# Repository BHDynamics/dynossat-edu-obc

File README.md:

# DynOSSAT-EDU-OBC (On-Board Computer)

**Important note: we have updated the Arduino Boards Manager link.** Please update your Arduino IDE settings with our new link: https://bhdynamics.github.io/board_index/package_bhdynamics_index.json since the previous one (https://bhdynamics.github.io/board_index/package_dynossat_index.json) **NO LONGER WORKS**.

DynOSSAT-EDU is the first open source PocketQube educational kit compatible with CircuitPython and Arduino.

This plaform is equipped with all the necessary modules for the operation of a nanosatellite (PocketQube)
in Low Earth Orbit (LEO) that would serve as a device for teaching, training, and driving curiosity about the philosophy and technology related to NewSpace.

This repository contains the hardware files for the OBC (On-Board Computer), the module responsible for managing the satellite and process sensor data. It
integrates a 9-axis IMU and carries a powerful ATSAMD51.

Hardware in this repository is licenced under **CERN OHL v1.2**.

## Technical details

- Powerful ATSAMD51J20A-AU 120 MHz Cortex-M4F processor with 1 MB flash + 256 KB RAM for all your CircuitPython needs
- 32 Mbit SPI flash for storing CircuitPython code and libraries
- High-precision ICM-20948 Inertial Measurement Unit including Accelerometer, Gyroscope and Magnetometer for Attitude management
- MCP9808 Digital Temperature Sensor
- SGP30 TVOC and eqCO2 air quality sensor
- User-controllable WS2812B addressable RGB LED
- Separate 5V and 3.3V rails, providing up to 1A/500mA respectively
- MicroSD Card slot
- Female USB-C 2.0 connector for power and data logging
- PQBH40 bus exposing 10 digital pins, 6 analog pins (+ true DAC), an I2C bus, an SPI bus and an UART

## Documentation

Available in this repo's [Wiki](https://github.com/BHDynamics/dynossat-edu-obc/wiki).

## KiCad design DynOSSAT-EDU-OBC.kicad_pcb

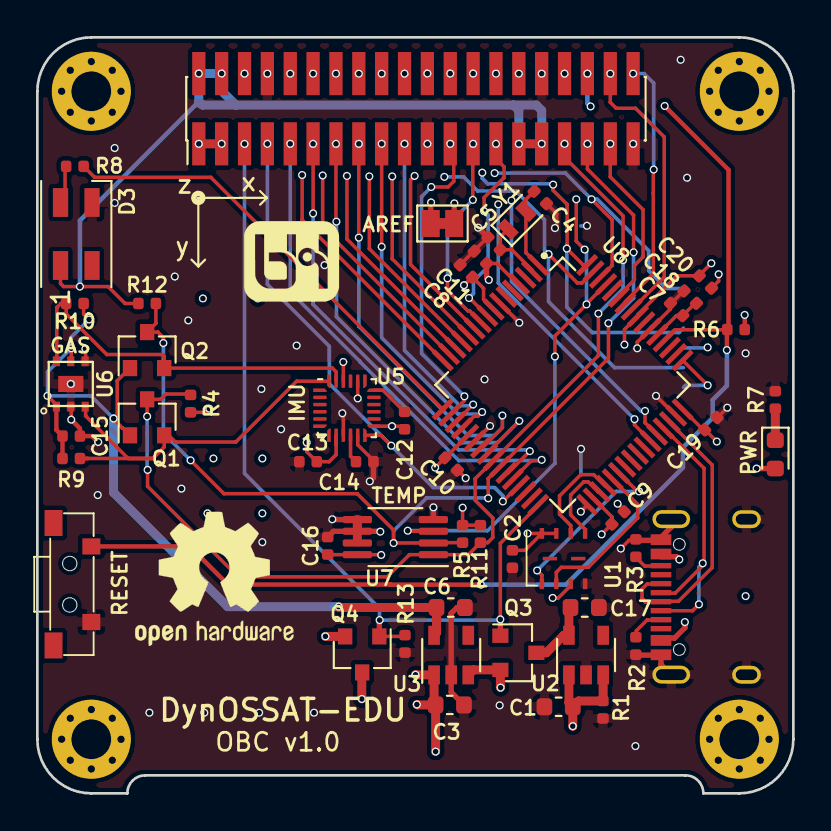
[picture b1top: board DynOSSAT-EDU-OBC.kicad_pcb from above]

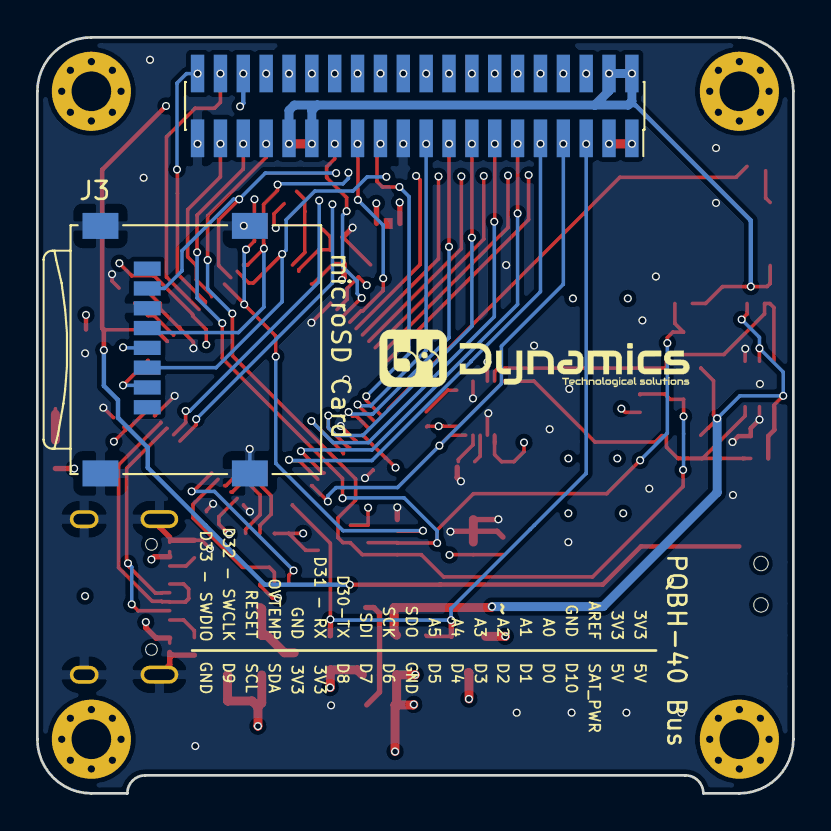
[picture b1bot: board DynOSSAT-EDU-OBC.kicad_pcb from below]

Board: 4 copper layers, 42.0 x 42.0 mm, 57 parts (2 on the bottom side), 54 nets.

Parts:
C1, C3, C6, C17: 10uF; C_0603_1608Metric
C2, C8, C11, C12, C13, C14, C15, C16, C18, C19, C20: 100nF; C_0402_1005Metric
C4, C5: 22pF; C_0402_1005Metric
C7, C9: 4.7uF; C_0402_1005Metric
C10: 1uF; C_0402_1005Metric
D2: Red; LED_0603_1608Metric
D3: WS2812B; LED_SK6812MINI_PLCC4_3.5x3.5mm_P1.75mm
H1, H2, H3, H4: MountingHole_Pad; MountingHole_2.2mm_M2_Pad_Via
J1: Main Bus; PinHeader_2x20_P1.27mm_Vertical_SMD
J2: Main Bus; PinSocket_2x20_P1.27mm_Vertical_SMD
J3: Micro_SD_Card; TF-102-18
J4: USB_C_Receptacle_USB2.0; U262-161N-4BVC11
JP2: Jumper; SolderJumper-2_P1.3mm_Bridged_Pad1.0x1.5mm
Q1, Q2: BSS138; SOT-23
Q3, Q4: DMG2305L; SOT-23
R1, R6, R13: 100k; R_0402_1005Metric
R2, R3: 5.1k; R_0402_1005Metric
R4, R5, R9, R10, R11, R12: 10k; R_0402_1005Metric
R7: 510; R_0402_1005Metric
R8: 510R; R_0402_1005Metric
SW1: RESET; 1TS002G-1800-3500-CT
U1: GD25Q32; WSON-8-1EP_3x4mm_P0.8mm
U2: ME6211C33; SOT-23-5
U3: ME6211C; SOT-23-5
U5: ICM-20948; QFN-24-1EP_3x3mm_P0.4mm_EP1.75x1.6mm
U6: SGP30
U7: MCP9808; MSOP-8_3x3mm_P0.65mm
U8: ATSAMD51J20A-AU; QFP50P1200X1200X120-64N
Y1: 32.768k - 12.5pF; Crystal_SMD_2012-2Pin_2.0x1.2mm

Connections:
+1V8: C6.1, C12.1, C13.1, C15.1, Q1.1, Q2.1, R9.1, R10.1, U3.5, U5.8, U5.13, U5.22, U6.1, U6.5
+3V3_SAT: C2.1, C3.1, C8.1, C9.1, C10.1, C16.1, C19.1, C20.1, D2.2, D3.1, J1.2, J1.4, J1.29, J1.31, J2.2, J2.4, J2.29, J2.31, J3.4, JP2.1, Q3.2, R4.2, R5.2, R6.2, R11.1, R12.1, U1.3, U1.7, U1.8, U3.1, U3.3, U7.8, U8.8, U8.21, U8.34, U8.48, U8.56
+5V_SAT: C1.1, J1.1, J1.3, J2.1, J2.3, Q4.2, R1.2, U2.1, U2.3
/A0: J1.10, J2.10, U8.16
/A1: J1.12, J2.12, U8.15
/A2: J1.14, J2.14, U8.14
/A3: J1.16, J2.16, U8.13
/A4: J1.18, J2.18, U8.12
/A5: J1.20, J2.20, U8.11
/AREF: C11.1, J1.6, J2.6, JP2.2, U8.4
/CS_FLASH: U1.1, U8.38
/D0: J1.9, J2.9, U8.28
/D1: J1.11, J2.11, U8.27
/D2: J1.13, J2.13, U8.24
/D3: J1.15, J2.15, U8.23
/D4: J1.17, J2.17, U8.20
/D5: J1.19, J2.19, U8.19
/D6: J1.23, J2.23, U8.18
/D7: J1.25, J2.25, U8.10
/D8: J1.27, J2.27, U8.9
/D9: J1.37, J2.37, U8.59
/LED: R8.1, U8.17
/RST: J1.36, J2.36, R6.1, SW1.1, U8.52
/RX: J1.30, J2.30, U8.44
/SAT_POWER: J1.5, J2.5, Q3.1, Q4.1, R13.2, U8.32
/SCK_FLASH: U1.6, U8.36
/SDI_FLASH: U1.2, U8.37
/SDO_FLASH: U1.5, U8.35
/SD_CS: J3.2, U8.49
/SPI_SCK: J1.24, J2.24, J3.5, U8.64
/SPI_SDI: J1.26, J2.26, J3.7, U8.62
/SPI_SDO: J1.22, J2.22, J3.3, U8.63
/SWCLK: J1.38, J2.38, U8.57
/SWDIO: J1.40, J2.40, U8.58
/Sensors/1V8_SCL: Q2.2, R10.2, U5.23, U6.6
/Sensors/1V8_SDA: Q1.2, R9.2, U5.24, U6.3
/TX: J1.28, J2.28, U8.43
/USB_D+: J4.A6, J4.B6, U8.46
/USB_D-: J4.A7, J4.B7, U8.45
GND: C1.2, C2.2, C3.2, C4.2, C5.2, C6.2, C7.2, C8.2, C9.2, C10.2, C11.2, C12.2, C13.2, C14.2, C15.2, C16.2, C17.2, C18.2, C19.2, C20.2, D3.3, J1.8, J1.21, J1.32, J1.39, J2.8, J2.21, J2.32, J2.39, J3.6, J3.9, J4.A1, J4.A12, J4.B1, J4.B12, J4.S1, R1.1, R2.1, R3.1, R7.1, R13.1, SW1.2, U1.4, U2.2, U3.2, U5.9, U5.11, U5.18, U5.20, U6.2, U6.4, U6.P$7, U7.4, U7.5, U7.6, U7.7, U8.7, U8.22, U8.33, U8.47, U8.54
IMU_INT: J1.7, J2.7, U5.12, U8.29
MCU_SCL: J1.35, J2.35, Q2.3, R5.1, R12.2, U7.2, U8.26
MCU_SDA: J1.33, J2.33, Q1.3, R4.1, R11.2, U7.1, U8.25
unnamed: C4.1, U8.1, Y1.2
unnamed: C5.1, U8.2, Y1.1
unnamed: C14.1, U5.10
unnamed: C17.1, Q3.3, U2.5
unnamed: C7.1, C18.1, U8.53
unnamed: D2.1, R7.2
unnamed: D3.4, R8.2
unnamed: J4.A5, R2.2
unnamed: J4.B5, R3.2
TEMP_ALERT: J1.34, J2.34, U7.3, U8.61
VBUS: J4.A4, J4.A9, J4.B4, J4.B9, Q4.3

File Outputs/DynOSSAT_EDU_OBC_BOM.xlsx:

Item | Qty | Reference(s) | Value | Part Number | Comments
1 | 4 | C1, C3, C6, C17 | 10uF |  | 0603 10uF X7R/X5R 10V or greater
2 | 11 | C2, C8, C11, C12, C13, C14, C15, C16, C18, C19, C20 | 100nF |  | 0402 100nF X7R/X5R 10V or greater
3 | 2 | C4, C5 | 22pF |  | 0402 22pF NP0/C0G
4 | 2 | C7, C9 | 4.7uF |  | 0402 4.7uF X7R/X5R 6.3V or greater
5 | 1 | C10 | 1uF |  | 0402 1uF X7R/X5R 10V or greater
6 | 1 | D2 | Red |  | 0603 LED Red
7 | 1 | D3 | WS2812B | WS2812B-MINI | RGB LED
8 | 1 | J1 | Main Bus PQBH40 | We don't have part numbers. Use generic connectors | Pin header male 1.27mm pitch 2x20 vertical SMD
9 | 1 | J2 | Main Bus PQBH40 | We don't have part numbers. Use generic connectors | Pin socket female 1.27mm pitch 2x20 vertical SMD
10 | 1 | J3 | Micro_SD_Card | TF-102-18 | Micro SD Card Holder
11 | 1 | J4 | USB_C_Receptacle_USB2.0 | U262-161N-4BVC11 | USB-C 2.0 connector - female socket
12 | 2 | Q1, Q2 | BSS138 | BSS138 | N-Channel MOSFET
13 | 2 | Q3, Q4 | DMG2305L | DMG2305UX-7 | P-Channel Power Mosfet
14 | 3 | R1, R6, R13 | 100k |  | 0402 100k 1%
15 | 2 | R2, R3 | 5.1k |  | 0402 5.1k 1%
16 | 2 | R4, R5 | 10k |  | 0402 10k 1%
17 | 2 | R7, R8 | 510R |  | 0402 510R 1%
18 | 4 | R9, R10, R11, R12 | 10k |  | 0402 10k 1%
19 | 1 | SW1 | RESET | 1TS002G-1800-3500-CT | Push Button side mount
20 | 1 | U1 | GD25Q32 | GD25Q32CNIGR | 32 Mbit flash memory SPI
21 | 1 | U2 | ME6211C33 | ME6211C33M5G-N | 3V3 LDO SOT-23-5
22 | 1 | U3 | ME6211C | ME6211C18M5G-N | 1V8 LDO SOT-23-5
23 | 1 | U5 | ICM-20948 | ICM-20948 | Inertial Measurement Unit
24 | 1 | U6 | SGP30 | SGP30-2.5k | VOC & eCO2 Gas Sensor
25 | 1 | U7 | MCP9808 | MCP9808T-E/MS | Package_SO:MSOP-8_3x3mm_P0.65mm
26 | 1 | U8 | ATSAMD51J20A-AU | ATSAMD51J20A-AU | MCU TQFP64
27 | 1 | Y1 | 32.768k - 12.5pF | X201232768KGD2SI | 2012 32768 kHz Crystal 12.5pF
For passives (resistors, capacitors, etc) you may use any quality brand while m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

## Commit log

2020-10-14 First commit, RC1.0
2020-10-16 Add README and LICENCE
2020-10-19 Update 3D models on MCU and button footprints
2020-11-06 Change MISO/MOSI for SDI/SDO
2020-11-06 Update hardware library to latest version
